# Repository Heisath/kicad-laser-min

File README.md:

## kicad-laser-min

The application will take a PCB file generated by KICAD and create paths isolating all nets.
This is isolation routing for PCBs.

### Version for Visual Studio 2019 and Windows

This fork has been adapted to compile easily on Windows using Visual Studio. All neccessary OpenCV libraries have been included so building should be as easy as possible.
The usage etc. explained below should still be valid, but might need to be changed a bit to accomodate powershell/cmd.

To be able to build and then directly start the application you will need the opencv dlls. They are included in kicadpcb2contour/opencv_dlls.7z but will need to be extracted to the containing folder. 

### Operation
The application uses a line Voronoi segmentation technique on the BW image of one layer of PCB. The Voronoi algorithm has been implemented in C++
by colorizing each track a different color. Each track is dilated until regions meet. Finally, an edge detection algorithm will produce the contours.
The contours produce the PCB region isolation. A contour following algorithm will transform the edge into gcode.

Double separation creates increase isolation between PCB tracks  (0.5mm per contour) .

The KICAD pcb to image conversion uses `<pxmm>` scale (which defaults to 30 pixels per mm).

Edge dilation takes time (why it is implemented in C++). The time is dependant on the `<pxmm>` scale.

Drill holes for pads and vias will be added to the end gcode. The holes drawn will be original size.

From left to right - BW Image of tracks, Colourized Dilation of tracks, Edge Detection of dilation.

## Note
The application is provided as is. I tested it with my own generated pcbs and worked well. However, your testing is also appreciated.
Please review outputs, especially gcode (as I am not an expert on any of the file formats used).

```KICAD Version used :
    Application: Pcbnew
    Version: 5.1.6-c6e7f7d~86~ubuntu18.04.1, release build
```

### Usage

```Usage:
Option: -m         Process map.png directly
        -f         Process Front Copper Layer.
        -b         Process Bottom and Front Copper Layer.
        -c         Do not cleanup after processing.
        -p<pxmm>   Change pixels per mm (default 30)
        -v        Don't Double Mark Vias
        -x        Mark Pads and Vias with '+'
        -d        Increase Separation between Isolated Zones
        -t       Increase Separation between Isolated Zones but include middle-trace
        -r       Override feedrate (default 120)
        -s		   Only draw single contours 
```

### Files
kicadpcb2contour.cpp

### Output Files
    map.png       - BW output image of Kicad PCB conversion
    cpp_image.png - your mind on LSD. The colorised image dilation of PCB tracks.
    trace.png     - Edge detection of the dilated image
    front.gcode   - Final gcode for Front Layer
    bottom.gcode  - Final gcode for Bottom Layer
    mask.png      - Mask of PCB to handle Edge cuts

### Dependencies
OpenCV libraries (version 4.5 used)  ( with opencv_contrib (ximgproc) disabled see issues)

### Compilation
Load into Visual Studio and press build/run

### Solved
Some offshoot tracks where created, output from opencv finContours. Contours outside the board are pruned out.

### Errors

However, as shown the inter-contour distance tolerance is of 0.0685mm. I have a laser cutter with an engraving width of 0.2mm (i.e. a
possible 0.1mm engraving width on the centre of track to a track coninciding from left or right side)

Contours do not touch.

However, distance is small enough to still function.

OpenCV follow contours creates two contours from both sides.
One could propose new findcontour method. No real problem here, rather than double time to process pcb.

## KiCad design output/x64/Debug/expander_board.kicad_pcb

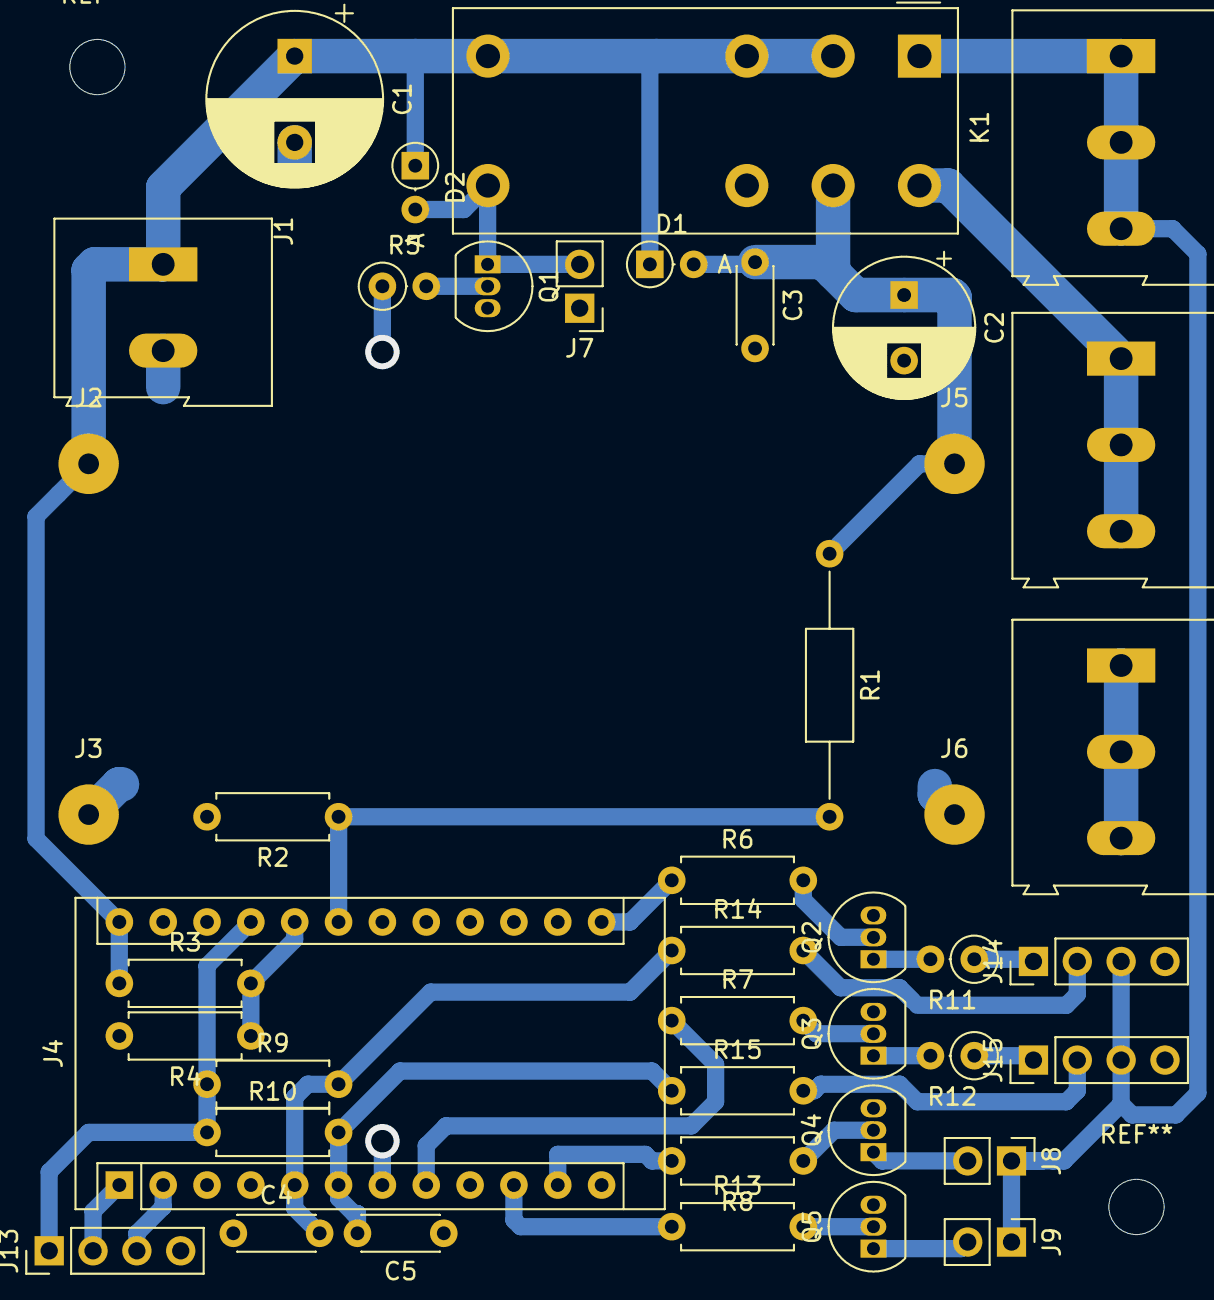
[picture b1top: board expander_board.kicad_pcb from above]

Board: 2 copper layers, 43 parts (0 on the bottom side), 31 nets.

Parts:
C1: 470µ; CP_Radial_D10.0mm_P5.00mm
C2: 220µ; CP_Radial_D8.0mm_P3.80mm
C3: 100n; C_Disc_D4.3mm_W1.9mm_P5.00mm
C4, C5: 1n; C_Disc_D4.3mm_W1.9mm_P5.00mm
D1: 1N4007; D_DO-35_SOD27_P2.54mm_Vertical_AnodeUp
D2: 1N4148; D_DO-35_SOD27_P2.54mm_Vertical_AnodeUp
J1: VIN; TerminalBlock_Altech_AK300-2_P5.00mm
J2: IN+; SolderWirePad_1x01_Drill1.2mm
J3: IN-; SolderWirePad_1x01_Drill1.2mm
J4: Arduino_Micro; Arduino_Pro_Micro
J5: OUT+; SolderWirePad_1x01_Drill1.2mm
J6: OUT-; SolderWirePad_1x01_Drill1.2mm
J7: AOn; PinHeader_1x02_P2.54mm_Vertical
J8, J9: Conn_01x02_Male; PinHeader_1x02_P2.54mm_Vertical
J10: 12V out; TerminalBlock_Altech_AK300-3_P5.00mm
J11: 5V out; TerminalBlock_Altech_AK300-3_P5.00mm
J12: GND out; TerminalBlock_Altech_AK300-3_P5.00mm
J13: Conn_01x04; PinHeader_1x04_P2.54mm_Vertical
J14: Fan_A; PinHeader_1x04_P2.54mm_Vertical
J15: Fan_B; PinHeader_1x04_P2.54mm_Vertical
K1: FTR F1CL012R; Relay_DPDT_Fujitsu_FTR-F1C
Q1, Q4, Q5: BC337; TO-92_Inline
Q2, Q3: BC546; TO-92_Inline
R1: 22k; R_Axial_DIN0207_L6.3mm_D2.5mm_P15.24mm_Horizontal
R2: 22k; R_Axial_DIN0207_L6.3mm_D2.5mm_P7.62mm_Horizontal
R3: 100k; R_Axial_DIN0207_L6.3mm_D2.5mm_P7.62mm_Horizontal
R4: 27k; R_Axial_DIN0207_L6.3mm_D2.5mm_P7.62mm_Horizontal
R5: 1k; R_Axial_DIN0207_L6.3mm_D2.5mm_P2.54mm_Vertical
R6, R7, R8, R13: 1k; R_Axial_DIN0207_L6.3mm_D2.5mm_P7.62mm_Horizontal
R9, R10: 100; R_Axial_DIN0207_L6.3mm_D2.5mm_P7.62mm_Horizontal
R11, R12: 100; R_Axial_DIN0207_L6.3mm_D2.5mm_P2.54mm_Vertical
R14, R15: 0; R_Axial_DIN0207_L6.3mm_D2.5mm_P7.62mm_Horizontal

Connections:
5v_ref: J4.A2, R1.2, R2.1
12v_ref: J4.A3, R3.2, R4.1
+5V: J11.1, J11.2, J11.3, K1.8
+5VD: J4.VCC, J13.1, R9.1, R10.1
+12V: J8.1, J9.1, J10.1, J10.2, J10.3, J14.3, J15.3, K1.1
AUX1: J4.8, R8.2
AUX2: J4.7, R13.1
Fan_Cntrl_A: J4.10, R6.1
Fan_Cntrl_B: J4.5, R7.1
Fan_RPM_A: C4.2, J4.2, R9.2, R14.1
Fan_RPM_B: C5.2, J4.3, R10.2, R15.1
GND: C1.2, C2.2, C3.2, C4.1, C5.1, J1.2, J3.1, J4.GND, J6.1, J7.1, J12.1, J12.2, J12.3, J13.4, J14.4, J15.4, Q1.3, Q2.3, Q3.3, Q4.3, Q5.3, R2.2, R4.2
unnamed: D2.2, J7.2, K1.5, Q1.1
unnamed: J8.2, Q4.1
unnamed: J9.2, Q5.1
unnamed: J14.1, R11.1
unnamed: J14.2, R14.2
unnamed: J15.1, R12.1
unnamed: J15.2, R15.2
unnamed: Q1.2, R5.2
unnamed: Q2.1, R11.2
unnamed: Q2.2, R6.2
unnamed: Q3.1, R12.2
unnamed: Q3.2, R7.2
unnamed: Q4.2, R8.1
unnamed: Q5.2, R13.2
RXD: J4.RxI, J13.3
Spg_ok: J4.4, R5.1
TXD: J4.TxD, J13.2
VCC: C1.1, D1.1, D2.1, J1.1, J2.1, J4.RAW, K1.2, K1.3, K1.4, R3.1
VDD: C2.1, C3.1, D1.2, J5.1, K1.7, R1.1

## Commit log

2020-12-23 Remove vscode artifacts
2020-12-23 Remove prebuilt linux executable
2020-12-23 Remove makefile Add folders containing opencv lib and includes
2020-12-23 Convert to Visual Studio project
    Former-commit-id: f0691551c271a5576786b9b4e6da80f5d52c7f41
2020-12-23 Remove ximgproc for easier build in windows
    Former-commit-id: 326018eb1d89753aaab1736e74b69aaca521dfe5
2020-12-23 Fix negation of unsigned by casting first
    Former-commit-id: 6e5c75501904234e42ce7c2df1f59300cb2289d8
2020-12-23 Fix color_pool overflow by increasing buffer
    Former-commit-id: 5a1165666a4d7e0052e3bba1e8d8fcf9371f4740
2020-12-23 Make use of Visual Studio DEBUG const
    Former-commit-id: 179cc4565ba4a5477f972c75789cbed01144a1b0
2020-12-23 Add output folder with released/precompiled program
    Former-commit-id: c941e77fcdfd2949a47b0d9024ad564a6377f9e4
2020-12-23 Update readme
    Former-commit-id: 75a90d4d5ab3b1fae1963c260dd0d682d5901e72
2020-12-23 Remove output files for github size limit
    Former-commit-id: b455f89159886f0e4e1cd67bd4c51e727ad269d2
2020-12-23 Update .gitignore
    Former-commit-id: b29e18df7edbbb49725d368426c420a09ebf7d8e
2020-12-23 Move opencv to 7z to meet github file restriction
    Former-commit-id: 48e3c6c65a911396432a8b839a79e1ba0a21caac
2020-12-23 Add switch to disable double contour Add thinning from ximgproc (disabled)
2020-12-24 Enable thinning and work around buffer underrun in gcode gen
2022-04-20 Prepare upstream changes
2022-04-20 Fixes for Visual Studio compilation
